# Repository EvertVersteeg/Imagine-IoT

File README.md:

Imagine-IoT! maker files repo!
=======================================

#### Imagine IOT Nodes firmware

## 01 ATmega 328p Boards
* IMN00x Nodes (Arduino-IDE)
* Imagine Bootloader
* PCB Boardfiles (KiCad)

## 02 Nordic nRF52840 Boards
* RAK WisBlock LPWAN Module (RAK4631) (Arduino-IDE)
* RAK Wishblock OTAA (TTN V3)
* RAK Wishblock BME680 (OLED)
* RAK Wishblock SHTC3
* TTN Payload decoder (for WisBlock)

## 03 ATtiny84 Boards
* ATTNode ATTiny84 (PlatformIO)
* Case (3D / SCAD)
* PCB Boardfiles (KiCad)

## 04 esp8266 Boards
* Wemos node (Wifi Localisation)

## 05 esp32 Boards
* P1 smart meter node (TTN Apeldoorn)

## 06 STM32 B-L072Z-LRWAN1
* Solar Node
* BeeHive node

## 07 STM32WL Boards
* STM32 Lora 1.0.3 node

## 08 MKR 1300
* With sensor ENV shield

## 09 Lora Field tester
* Lora tester with display

## 10 Discovery Boards
* STM32F407 Discovery Kit

## 20 NUCLEO Boards
* NUCLEO-G071RB
* NUCLEO-H723ZG
* NUCLEO-L476RG
* NUCLEO-L053R8
 
## 30 DevEUI chips
* 24AA02E64-I-SN

License
=======
The files in this repository are distributed under various licenses.
Each file lists the license that applies to it, with the exception of
the bootloader binaries. These are distributed under the GPLv2, see
https://github.com/Optiboot/optiboot for the full terms and the sources
used to compile the bootloader (see the commit log of this repository to
find out the exact version used).

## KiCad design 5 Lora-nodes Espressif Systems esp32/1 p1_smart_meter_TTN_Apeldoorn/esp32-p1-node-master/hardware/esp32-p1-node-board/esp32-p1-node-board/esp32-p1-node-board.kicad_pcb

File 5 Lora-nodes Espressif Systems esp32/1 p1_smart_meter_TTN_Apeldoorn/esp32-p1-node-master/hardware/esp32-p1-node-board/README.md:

# TTN-Apeldoorn P1-Node Hardware

## TTN-Apeldoorn P1-Node Hardware settings
THe board has tree hardware settings:
JP1: selection between hard and software serial, default soft serial
=> You must use Hardware Serial if baudrate > 57.6K
JP2: selection between soft and hard request, default hard request.
=> Data_Req signal to P1 is always high (reading active)
JP3: Selection between yes/no change polarity.

## TTGO LoRa32 SX1276 OLED Overview
The TTGO LoRa32 SX1276 OLED is a development board with an ESP32, a built-in LoRa chip and an SSD1306 OLED display.

## TTGO LoRa32 SX1276 OLED Pins
The following figure shows the TTGO LoRa32 OLED board pinout.

The OLED displays communicates using I2C communication protocol. It is internally connected to the ESP32 on the following pins:
* SDA	GPIO 4
* SCL	GPIO 15
* RST	GPIO 16

The SX1276 LoRa chip communicates via SPI communication protocol, and it is internally connected to the ESP32 on the following GPIOs:
* MISO	GPIO 19
* MOSI	GPIO 27
* SCK	GPIO 5
* CS	GPIO 18
* IRQ	GPIO 26
* RST	GPIO 14

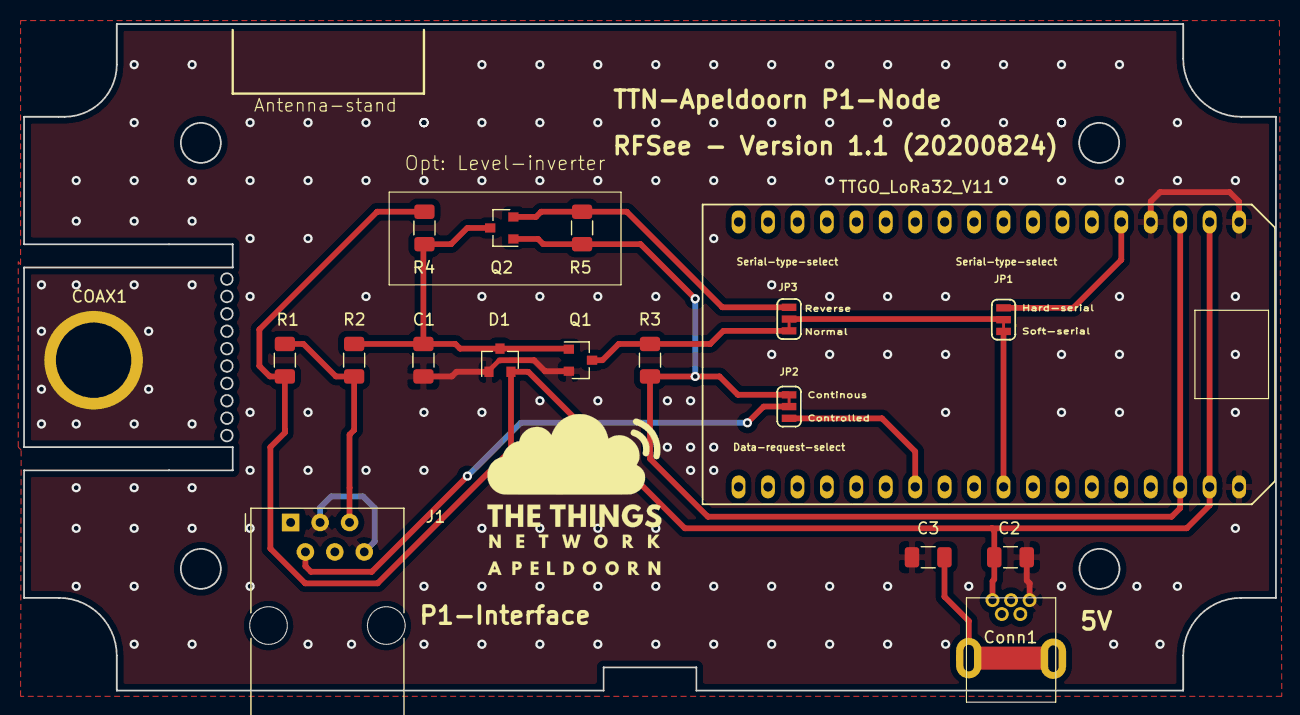
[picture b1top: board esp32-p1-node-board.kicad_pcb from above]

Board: 2 copper layers, 108.0 x 57.5 mm, 18 parts (0 on the bottom side), 13 nets.

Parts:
C1, C2, C3: 10n; C_1206_3216Metric
COAX1: SMA-ANT-CONN
Conn1: THT_USB-B-Mini
D1: BAT54S; SOT-23
J1: RJ11-6; RJ12_Amphenol_54601
JP1, JP3: Serial-type-select; SMT-JUMPER_3_1-NC_TRACE_SILK
JP2: Data-request-select; SMT-JUMPER_3_1-NC_TRACE_SILK
Q1: BC847; SOT-23
Q2: BSS138; SOT-23
R1, R4, R5: 10K; R_1206_3216Metric
R2: 1K; R_1206_3216Metric
R3: 12K; R_1206_3216Metric
U1: TTGO_LoRa32_V11

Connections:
/3V3: JP2.3, Q2.1, R3.1, R5.1, U1.3, U1.34
/5V: C2.1, Conn1.1, D1.2, R1.1, R4.1, U1.2, U1.35
/DATA: J1.5, R1.2, R2.2
/DATA_3V3: JP1.2, JP3.2
/DATA_3V3_N: JP3.3, Q1.3, R3.2
/DATA_5V_R: C1.1, D1.3, Q1.1, Q2.3, R2.1, R4.2
/DATA_GND: C1.2, C2.2, C3.1, COAX1.1, Conn1.5, D1.1, J1.3, J1.6, Q1.2, U1.1, U1.4, U1.36
/DATA_REQ: J1.2, JP2.2
/HARD_RXD: JP1.1, U1.5
/SOFT_REQ: JP2.1, U1.25
/SOFT_RXD: JP1.3, U1.28
unnamed: C3.2, Conn1.6, Conn1.7
unnamed: JP3.1, Q2.2, R5.2

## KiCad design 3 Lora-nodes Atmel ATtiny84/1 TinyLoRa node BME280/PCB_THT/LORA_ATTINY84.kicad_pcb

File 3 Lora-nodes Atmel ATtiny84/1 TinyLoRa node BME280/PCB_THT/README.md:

# ATTNode PCB (Throughole Version)

**Further Development will be for the SMD Version. At the Moment I don't plan amy further developing the THT Version**

PCB for the ATTiny Sensor Node, Throughole Version 
WARNING: Due to height might not fit into the 3D-Printed case when ATTiny is used with a Socket

## Parts List

*  ATTiny84A-PU (DIL-14) MCU
*  HopeRF RFM95W Lora Module
*  SMD CR2032 Battery Holder (see pictures in main directory for type I used)
*  Small antenna for 868MHz (or the LoRa band used in your region)
*  1x8 Pin 2.54mm Pitch Pinheader for J1 (only if not meant to be put into the case), optional

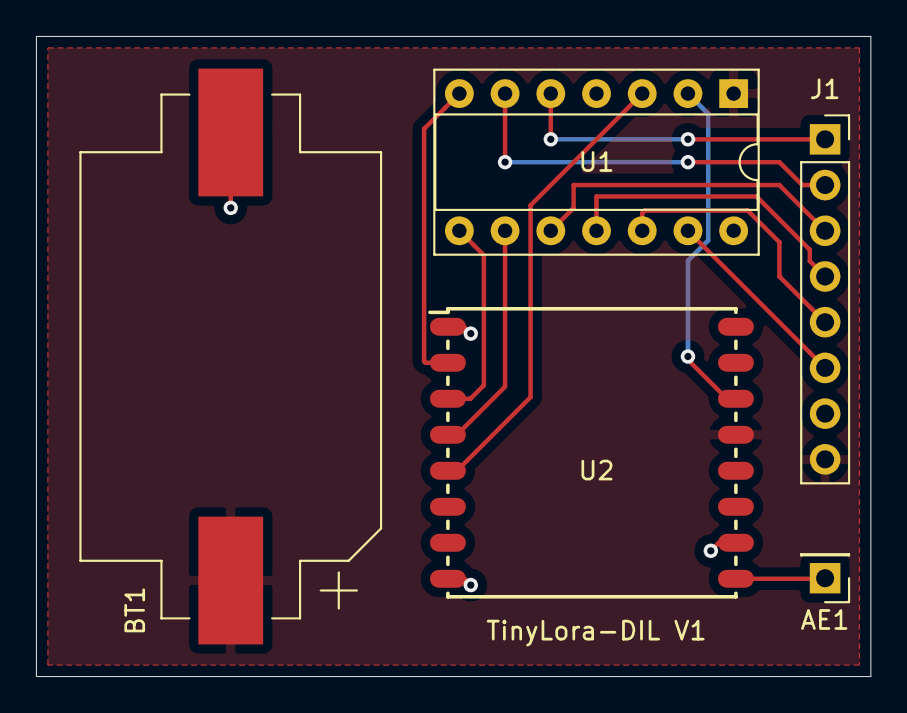
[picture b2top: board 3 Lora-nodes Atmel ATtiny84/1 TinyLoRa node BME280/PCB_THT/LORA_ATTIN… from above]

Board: 2 copper layers, 46.4 x 35.6 mm, 5 parts (0 on the bottom side), 14 nets.

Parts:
AE1: Antenna; PinHeader_1x01_P2.54mm_Vertical
BT1: Battery_Cell; BatteryHolder_Keystone_1060_1x2032_Long_Pad
J1: Sensor; PinSocket_1x08_P2.54mm_Vertical
U1: ATtiny84A-SSU; DIP-14_W7.62mm_Socket
U2: RFM95W-868S2; RFM95

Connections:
+3V3: BT1.1, J1.8, U1.1, U2.13
DIO0: U1.2, U2.14
GND: BT1.2, J1.7, U1.14, U2.1, U2.8, U2.10
MISO: U1.8, U2.3
MOSI: U1.7, U2.2
NSS: U1.3, U2.5
unnamed: AE1.1, U2.9
PA0: J1.6, U1.13
PA1: J1.5, U1.12
PA2: J1.4, U1.11
PA3: J1.3, U1.10
PA7: J1.2, U1.6
PB2: J1.1, U1.5
SCK: U1.9, U2.4

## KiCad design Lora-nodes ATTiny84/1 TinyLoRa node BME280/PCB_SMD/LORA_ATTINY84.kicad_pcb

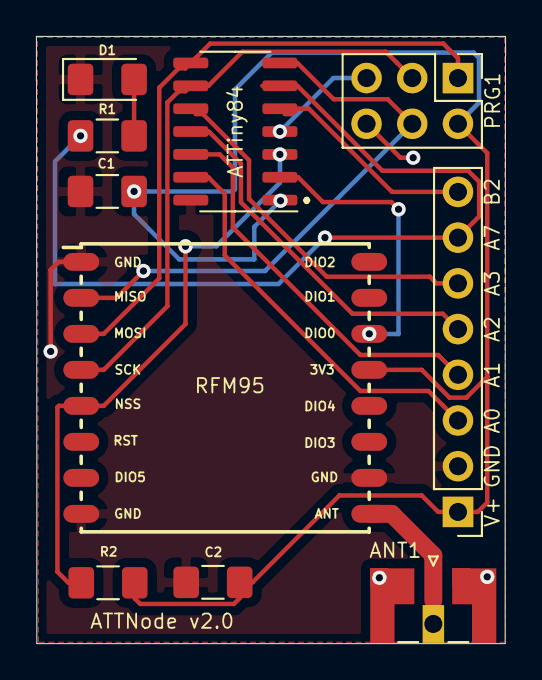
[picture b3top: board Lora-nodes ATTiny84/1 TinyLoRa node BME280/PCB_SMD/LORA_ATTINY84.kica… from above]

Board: 2 copper layers, 26.1 x 33.7 mm, 11 parts (1 on the bottom side), 16 nets.

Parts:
ANT1: Antenna; SMA_Edge_UFL_Combo
ATTiny84: ATtiny84A-SSU; SOIC-14_3.9x8.7mm_P1.27mm
BAT1: Battery_Cell; BatteryHolder_Keystone_1060_1x2032_Long_Pad
C1, C2: 100n; C_1206_3216Metric_Pad1.42x1.75mm_HandSolder
D1: LED; LED_1206_3216Metric_Pad1.42x1.75mm_HandSolder
J1: J1; PinHeader_1x08_P2.54mm_Vertical
PRG1: PRG; PinHeader_2x03_P2.54mm_Vertical
R1: 100; R_1206_3216Metric_Pad1.42x1.75mm_HandSolder
R2: 47K; R_1206_3216Metric_Pad1.42x1.75mm_HandSolder
RFM95: RFM95W-868S2; RFM95

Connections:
+3V3: ATTiny84.1, BAT1.1, C1.1, C2.1, J1.1, PRG1.2, R2.2, RFM95.13
DIO0: ATTiny84.2, RFM95.14
GND: ANT1.2, ATTiny84.14, BAT1.2, C1.2, C2.2, D1.1, J1.2, PRG1.6, RFM95.1, RFM95.8, RFM95.10
MISO: ATTiny84.8, PRG1.1, RFM95.3
MOSI: ATTiny84.7, PRG1.4, RFM95.2
NSS: ATTiny84.3, R2.1, RFM95.5
unnamed: ANT1.1, RFM95.9
unnamed: D1.2, R1.1
PA0: ATTiny84.13, J1.3
PA1: ATTiny84.12, J1.4
PA2: ATTiny84.11, J1.5
PA3: ATTiny84.10, J1.6
PA7: ATTiny84.6, J1.7, R1.2
PB2: ATTiny84.5, J1.8
RST: ATTiny84.4, PRG1.5
SCK: ATTiny84.9, PRG1.3, RFM95.4

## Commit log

2020-10-11 Added IM001
2020-10-11 IMN001 update
2020-10-13 Added NUCLEO-L476RG Blinky
2020-10-13 Added READme
2020-10-13 Added Alt Flash LEDS
2020-10-14 Updated READme + license files
2020-10-15 Added assembly example
2020-10-17 Update READme + new project files
2020-10-17 Added Bootloader files
2020-10-18 Added blinky
2020-10-18 Added Project
    Random Flashing LEDs
2020-12-01 Update files
2020-12-01 Changed to Unconfirmed packet definition, removed old keys
2020-12-01 Added new node software
2020-12-01 Added Wemos Wifi Localisation
2020-12-08 Added indoor enclosure (RAK)
2020-12-14 Added p1 node, changed file structure
2020-12-14 Update file structure
2020-12-17 Added IMN003
2020-12-17 Added node IMN005
2020-12-17 Added node IMN006
2020-12-18 Added jpg of board
2020-12-18 Added pins jpg
2020-12-18 Added data to P1 node
2020-12-24 Added datasheets + schematics
2020-12-25 Update node P1: BOM
2020-12-26 Added v1.2 software DSM
2020-12-29 Added Datacake payload files
2020-12-30 Added 7-segment controller
2020-12-30 Added datasheet transistor
2020-12-30 Added two Digit example
2020-12-30 Added 2 digit counter (button triggered)
2021-02-06 Added datasheets
2021-02-06 Added zip file
2021-02-13 Added RAK Wishnode OTAA example
2021-02-13 Added Solar node
2021-02-13 Added readme files
2021-02-14 Added Flashing LED program with STM32CubeIDE
2021-02-14 Use off internal crystal 8MHz added
2021-02-14 Added directory
2021-02-14 Added new project Alternate LEDs
2021-02-14 Added program files
2021-03-08 Added I2C Eeprom example
2021-03-10 Added debug example code
2021-03-13 Added debug header file
2021-03-13 Added FreeRTOS example
2021-03-21 Added Port Expander project
2021-03-21 Added project files IO expander
2021-03-22 Added GCC compiler install instructions (Windows 10 Pro)
2021-03-29 Added board and structure padding example
2021-03-30 Added example and data discovery kit
2021-04-02 Added printf ITM SWV example STM32f4
2021-04-02 Added inline assembly example
2021-04-02 Updated inline assambly example
2021-04-02 Added access level example
2021-04-02 Added some Macros
2021-04-04 Added bit banding
2021-04-12 Added 3D case
2021-04-16 Added Bit Banding example
2021-04-17 Added task schedular
2021-04-29 Updated ATtiny repo
2021-05-01 Added Field tester files
2021-05-02 Added make file example
2021-05-02 Updated startup file
2021-05-03 Added linkerfile
2021-05-05 Update file locations
2021-05-05 added reset handler
2021-05-05 Added download to target
2021-05-05 added update
2021-05-08 Updated datasheets
2021-05-08 Added HSI clock example
2021-05-14 Added WIO board file
2021-05-15 Added default program
2021-05-15 Updated default program
2021-05-16 Added driver file
2021-05-16 Updated drivers header file
2021-05-17 Updated comments + removed main.h
2021-05-25 Added GPIO driver files
2021-05-28 Added datasheets BeeHive project
2021-06-09 Updated comments
2021-06-09 Fixed input parameters GPIO APIs
2021-06-09 Implemented GPIO_PeriClockControl function
2021-06-28 First two assembly examples
2021-06-28 Renamed maps
2021-06-28 Updated assembly examples
2021-06-29 Added new project
2021-07-01 Min max search example
2021-07-01 Example 1.4 sum of elements in an array in assembly
2021-07-01 Added board files
2021-07-06 ip_example
2021-07-06 DevEUI
2021-07-06 Added EUI-64 example and pinout
2021-07-13 Macros and function defenition (GPIO API)
2021-07-13 Init GPIO API function definition
2021-07-13 GPIO_Init function definition
2021-07-13 GPIO de-init API implementation
2021-07-14 GPIO API read input pin / port function
2021-07-16 Compile binary
2021-07-16 GPIO API write to output pin or port function
2021-07-16 compiler binary
2021-07-16 GPIO API toggle output pin function
2021-07-16 Toggle green LED with GPIO API
2021-07-17 Second LED
2021-07-18 GPIO LED toggle API excample with Btn
2021-07-18 Final GPIO API
2021-07-18 GPIO API configure interrupt EXTCR peripheral side
2021-07-19 GPIO API IRQ number macros
2021-07-19 GPIO API IRQ priority function
2021-07-26 EUI64 print nice
2021-08-07 MKR 1300 board files
2021-08-08 Structure maps
2021-08-08 changed maps
2021-08-08 ENV shield example + datasheets
2021-08-10 Removed UV sensor (not present on R2 ENV board)
2021-08-10 Datasheet
2021-08-10 Store data to SD in CSV file
2021-08-10 Timestamp to CSV and in filename
2021-08-11 DownLink options
2021-08-11 Datasheets and schedule of board
2021-08-11 Cayennelpp, ENV shield sensors and SD card logger
2021-08-12 3D stand
2021-08-20 MKR WAN sketches
2021-08-24 MKR1300 Lightsensor
2021-08-26 Dali + AT commands
2021-08-26 LoRaRadar
2021-08-26 LoRaLightSensor MKR1300
2021-08-27 Dali
2021-08-30 VEML7700
2021-09-13 VEML7700 data
2021-09-13 NPN Data
2021-09-13 Light meter
2021-09-16 Dali busTest function
2021-09-23 CAN update lower bus freq
2021-11-04 Can bus program update
2021-12-18 Update CAN software
2022-07-09 General update

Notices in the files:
5 Lora-nodes Espressif Systems esp32/1 p1_smart_meter_TTN_Apeldoorn/esp32-p1-node-master/hardware/esp32-p1-node-board/esp32-p1-node-board/esp32-p1-node-board.kicad_pcb:
CC BY-NC-SA 3.0 NL
